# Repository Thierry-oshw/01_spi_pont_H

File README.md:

# 01_spi_pont_H
module pont H commandé en SPI // H bridge SPI drived module  

Version 2.0 of the CERN Open Hardware Licence: cern_ohl_p_v2.txt

Here picture as of 31/01/2021:

2021 05 21: la puce est obsolète.
L'utilisation en statique est bien.
Faire un pont H qui pilote un moteur oblige à "bombarder" le bus spi.

La carte est abandonnée.

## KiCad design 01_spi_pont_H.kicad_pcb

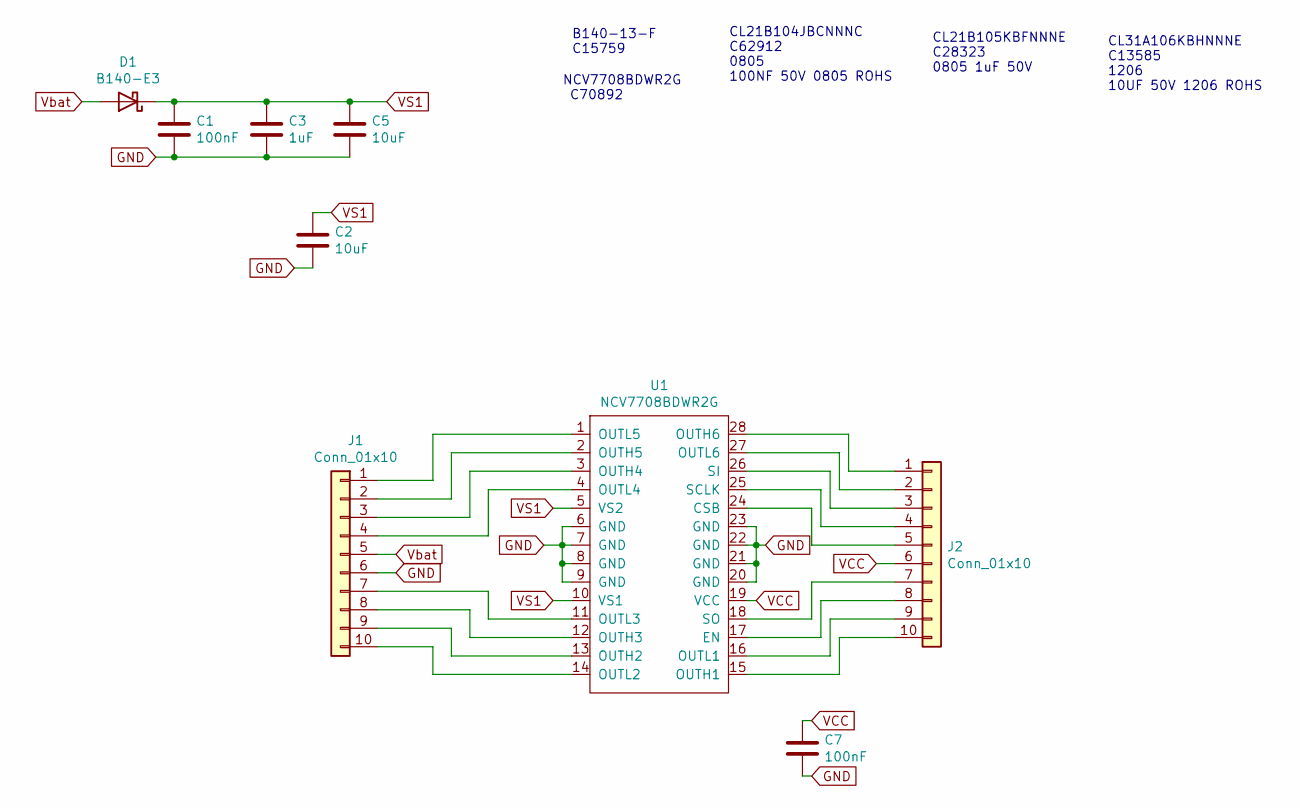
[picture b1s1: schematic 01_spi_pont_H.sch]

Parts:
C1, C7: 100nF; C_0805_2012Metric
C2, C5: 10uF; C_1206_3216Metric
C3: 1uF; C_0805_2012Metric
D1: B140-E3; D_SMA
J1, J2: Conn_01x10; PinHeader_1x10_P2.54mm_Vertical
U1: NCV7708BDWR2G; SOIC-28W_7.5x17.9mm_P1.27mm

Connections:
GND: C1.2, C2.2, C3.2, C5.2, C7.2, J1.6, U1.6 (GND), U1.7 (GND), U1.8 (GND), U1.9 (GND), U1.20 (GND), U1.21 (GND), U1.22 (GND), U1.23 (GND)
unnamed: J1.1, U1.1 (OUTL5)
unnamed: J1.2, U1.2 (OUTH5)
unnamed: J1.3, U1.3 (OUTH4)
unnamed: J1.4, U1.4 (OUTL4)
unnamed: J1.7, U1.11 (OUTL3)
unnamed: J1.8, U1.12 (OUTH3)
unnamed: J1.9, U1.13 (OUTH2)
unnamed: J1.10, U1.14 (OUTL2)
unnamed: J2.1, U1.28 (OUTH6)
unnamed: J2.2, U1.27 (OUTL6)
unnamed: J2.3, U1.26 (SI)
unnamed: J2.4, U1.25 (SCLK)
unnamed: J2.5, U1.24 (CSB)
unnamed: J2.7, U1.18 (SO)
unnamed: J2.8, U1.17 (EN)
unnamed: J2.9, U1.16 (OUTL1)
unnamed: J2.10, U1.15 (OUTH1)
VCC: C7.1, J2.6, U1.19 (VCC)
VS1: C1.1, C2.1, C3.1, C5.1, D1.1 (K), U1.5 (VS2), U1.10 (VS1)
Vbat: D1.2 (A), J1.5

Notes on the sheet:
B140-13-F C15759
NCV7708BDWR2G C70892
CL21B105KBFNNNE C28323 0805 1uF 50V
CL21B104JBCNNNC C62912 0805 100NF 50V 0805 ROHS
CL31A106KBHNNNE C13585 1206 10UF 50V 1206 ROHS

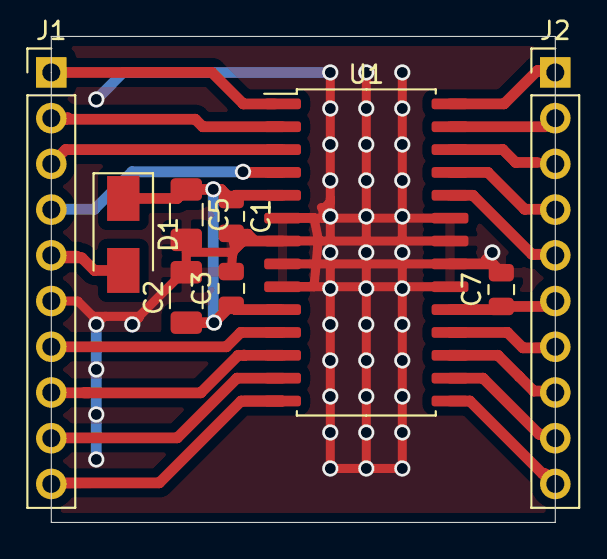
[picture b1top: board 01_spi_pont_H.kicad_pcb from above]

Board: 2 copper layers, 28.0 x 27.0 mm, 9 parts (0 on the bottom side), 21 nets.

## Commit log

2020-11-21 Add files via upload
    initial
2020-11-30 Delete fp-info-cache
    No need for this huge file.
2020-12-06 gitignore set to kicad version
2021-01-02 removed useless files
2021-01-30 added picture
2021-05-21 Update README.md
    obsolète
2021-07-23 maj librairie
2023-05-02 chgt nom fichier licence
